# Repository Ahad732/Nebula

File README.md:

# RP2040 Devboard
I have made a devboard with RP 2040 microcontroller. It has 16 mb storage and its just like a raspberry pi pico but in my design. I had build it off a guide from macondo.I built it to learn hardware. This was my first hardware project for hackclub. It has a usb type C port that is used everywhere nowadays.

Features :
16 Mbit Storage    
Bootsel button  
Uses the popular RP2040 microcontroller    
Can be easily coded for custom projects and inovative ideas  
Open-source so anyone can use the design and order their board  
Has 2 leds, a power and a gpio led  

|Designator                                |Footprint                                  |Value                      |Quantity                   |Price                |Link                                                                                                                                                                 |
|------------------------------------------|-------------------------------------------|---------------------------|---------------------------|---------------------|---------------------------------------------------------------------------------------------------------------------------------------------------------------------|
|C1_2, C1, C10                             |402                                        |C 1uf                      |125                        |0.1                  |https://robu.in/product/cl05a105kq5nnwc-samsung-electro-mechanics-multilayer-ceramic-capacitors-mlcc-smd-smt-1uf-10-6-3v-x5r-1-0402/                                 |
|C11, C12, C3, C4, C5, C6, C7, C8, C9_2, C9|402                                        |C0.1uf                     |ALREADY HAVE               |---------------------|https://robu.in/product/0402b104j100ct-walsin-smd-multilayer-ceramic-capacitor-general-purpose-0-1-%c2%b5f-10-v-0402-1005-metric-%c2%b1-5-x7r/                       |
|C14                                       |603                                        |10 uF                      |ALREADY HAVE               |---------------------|https://robu.in/product/tcc0603x5r106m100ct-cctc-smt-ceramic-capacitors-0603-x5r-106m10%c2%b5f%c2%b120-rated-voltage10v-thickness0-80mm-tape/                        |
|C15, C16                                  |402                                        |33pF                       |30                         |0.11                 |https://robu.in/product/0402hq330j500nb-fh-smd-multilayer-ceramic-capacitor-33-pf-50-v-0402-1005-metric-%c2%b1-5-c0g/                                                |
|J1                                        |USB_C_Receptacle_XKB_U262-16XN-4BVC11      |USB_C_Receptacle_USB2.0_16P|ALREADY HAVE               |---------------------|https://www.lcsc.com/product-detail/C393939.html?s_z=n_q_c393939&globalKeyword=c393939                                                                               |
|J2, J3                                    |PinHeader_1x20_P2.54mm_Vertical            |Conn_01x20                 |2                          |DNP                  |                                                                                                                                                                     |
|J4                                        |PinHeader_1x03_P2.54mm_Vertical            |Conn_01x03                 |1                          |DNP                  |                                                                                                                                                                     |
|R1, R2                                    |402                                        |5.1K                       |100                        |0.11                 |https://robu.in/product/rc0402fr-075k1l-yageo-smd-chip-resistor/                                                                                                     |
|R3, R4                                    |402                                        |27                         |35                         |0.12                 |https://robu.in/product/0402wgj0270tce-uniohm-royal-ohm-62-5mw-thick-film-resistors-50v%c2%b1100ppm-%e2%84%83-%c2%b15-27%cf%89-0402-chip-resistor-surface-mount-rohs/|
|R5, R6, R7, R8                            |402                                        |1K                         |30                         |0.11                 |https://robu.in/product/wr04x1001ftl-walsin-62-5mw-thick-film-resistors-50v-%c2%b1100ppm-%e2%84%83-%c2%b11-1k%cf%89-0402-chip-resistor-surface-mount-rohs/           |
|R7                                        |402                                        |10K                        |85                         |0.11                 |https://robu.in/product/rc0402fr-0710kl-yageo-res-thick-film-0402-10k-ohm-1-0-063w1-16w-%c2%b1100ppm-c-pad-smd-t-r/                                                  |
|SW1                                       |Button_Switch_SMD:SW_SPST_PTS810           |SW_Push                    |5                          |0.99                 |https://robu.in/product/pts810sjg250smtrlfs-ck-3-2mm-2-5mm-round-button-50ma-standing-paste-4-2mm-spst-400gf-16v-smd-4p3-2x4-2mm-tactile-switches-rohs/              |
|U1                                        |QFN-56-1EP_7x7mm_P0.4mm_EP3.2x3.2mm        |RP2040                     |2                          |1.33                 |https://robu.in/product/raspberry-pi-rp2040/                                                                                                                         |
|U2                                        |Winbond_USON-8-1EP_3x2mm_P0.5mm_EP0.2x1.6mm|APS1604M-3SQRx-ZR          |2                          |4.88                 |https://www.lioncircuits.com/parts/IS25WP016D-JULE-TR                                                                                                                |
|U4                                        |SOT-23                                     |MCP1700x-330xxTT           |2                          |1.05                 |https://www.lioncircuits.com/parts/MCP1700T-3302E%2FTT                                                                                                               |
|Y1                                        |Crystal_SMD_3225-4Pin_3.2x2.5mm            |Crystal_GND24              |2                          |1.23                 |https://www.lioncircuits.com/parts/ECS-120-20-33-CKM-TR                                                                                                              |
|D1, D2                                    |Led                                        |402                        |----------------------     |ALREADY HAVE         |---------------------                                                                                                                                                |
|                                          |                                           |                           |Tools Required For Building|22.88                |https://robu.in/product/yihua-8858-v-hot-air-station-nozzles-stand/                                                                                                  |
|                                          |                                           |                           |PCB Cost + Shipping        |9.29                 |                                                                                                                                                                     |
|                                          |                                           |                           |Parts Shipping             |1.55                 |                                                                                                                                                                     |
|                                          |                                           |                           |Total                      |43.86                |                                                                                                                                                                     |

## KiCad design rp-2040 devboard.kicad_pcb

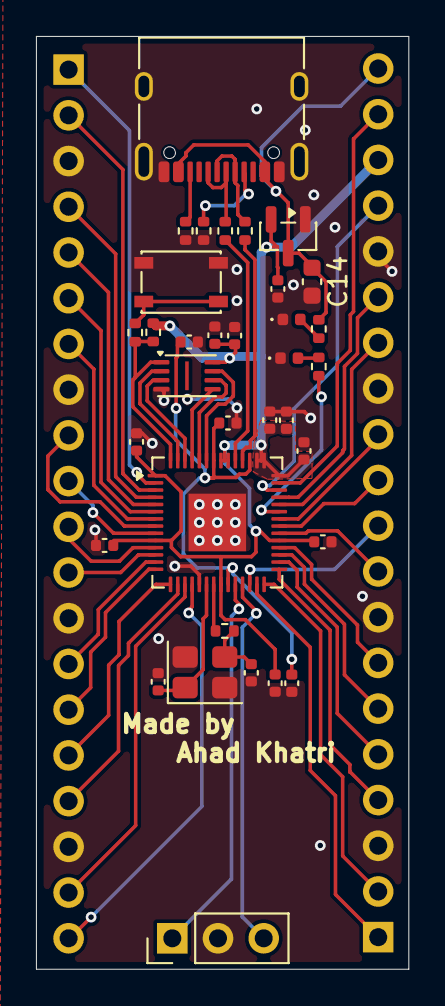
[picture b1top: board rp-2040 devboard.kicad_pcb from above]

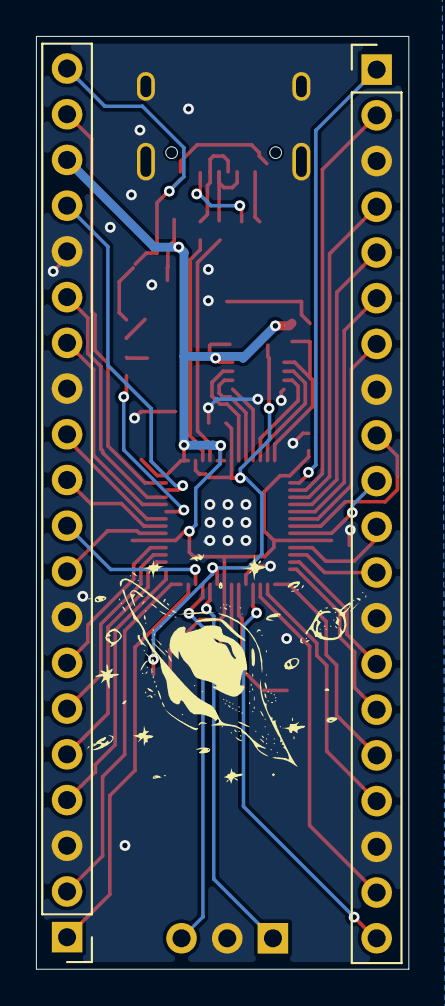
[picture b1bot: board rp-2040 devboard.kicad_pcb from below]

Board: 2 copper layers, 20.7 x 51.8 mm, 36 parts (2 on the bottom side), 55 nets.

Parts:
C1, C1#2, C10: C 1uf; C_0402_1005Metric
C3, C4, C5, C6, C7, C8, C9, C9#2, C11, C12: C0.1uf; C_0402_1005Metric
C14: 10 uF; C_0603_1608Metric
C15, C16: 33pF; C_0402_1005Metric
D1, D2: LED; LED_0402_1005Metric
J1: USB_C_Receptacle_USB2.0_16P; USB_C_Receptacle_XKB_U262-16XN-4BVC11
J2, J3: Conn_01x20; PinHeader_1x20_P2.54mm_Vertical
J4: Conn_01x03; PinHeader_1x03_P2.54mm_Vertical
R1, R2: 5.1K; R_0402_1005Metric
R3, R4: 27; R_0402_1005Metric
R5, R6, R8, R9: 1K; R_0402_1005Metric
R7: 10K; R_0402_1005Metric
SW1: SW_Push; SW_SPST_PTS810
U1: RP2040; QFN-56-1EP_7x7mm_P0.4mm_EP3.2x3.2mm
U2: APS1604M-3SQRx-ZR; Winbond_USON-8-1EP_3x2mm_P0.5mm_EP0.2x1.6mm
U4: MCP1700x-330xxTT; SOT-23
Y1: Crystal_GND24; Crystal_SMD_3225-4Pin_3.2x2.5mm

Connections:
+1V1: C10.1, C11.1, C12.1, U1.23 (DVDD), U1.45 (VREG_VOUT), U1.50 (DVDD)
+3V3: C1.1, C1#2.1, C3.1, C4.1, C5.1, C6.1, C7.1, C8.1, C9.1, C9#2.1, J3.18, R7.2, U1.1 (IOVDD), U1.10 (IOVDD), U1.22 (IOVDD), U1.33 (IOVDD), U1.42 (IOVDD), U1.43 (ADC_AVDD), U1.44 (VREG_VIN), U1.48 (USB_VDD), U1.49 (IOVDD), U2.8 (VDD), U4.2 (VO)
GND: C1.2, C1#2.2, C3.2, C4.2, C5.2, C6.2, C7.2, C8.2, C9.2, C9#2.2, C10.2, C11.2, C12.2, C14.2, C15.1, C16.1, D1.1 (K), D2.1 (K), J1.A1 (GND), J1.A12 (GND), J1.B1 (GND), J1.B12 (GND), J1.SH (SHIELD), J2.3, J2.8, J2.13, J2.18, J3.3, J3.8, J3.13, J3.16, J4.2, R1.1, R2.1, SW1.1, U1.19 (TESTEN), U1.57 (GND), U2.4 (VSS), U4.1 (GND), Y1.2 (G), Y1.4 (G)
GPIO0: J2.1, U1.2 (GPIO0)
GPIO1: J2.2, U1.3 (GPIO1)
GPIO2: J2.4, U1.4 (GPIO2)
GPIO3: J2.5, U1.5 (GPIO3)
GPIO4: J2.6, U1.6 (GPIO4)
GPIO5: J2.7, U1.7 (GPIO5)
GPIO6: J2.9, U1.8 (GPIO6)
GPIO7: J2.10, U1.9 (GPIO7)
GPIO8: J2.11, U1.11 (GPIO8)
GPIO9: J2.12, U1.12 (GPIO9)
GPIO10: J2.14, U1.13 (GPIO10)
GPIO11: J2.15, U1.14 (GPIO11)
GPIO12: J2.16, U1.15 (GPIO12)
GPIO13: J2.17, U1.16 (GPIO13)
GPIO14: J2.19, U1.17 (GPIO14)
GPIO15: J2.20, U1.18 (GPIO15)
GPIO16: J3.1, U1.27 (GPIO16)
GPIO17: J3.2, U1.28 (GPIO17)
GPIO18: J3.4, U1.29 (GPIO18)
GPIO19: J3.5, U1.30 (GPIO19)
GPIO20: J3.6, U1.31 (GPIO20)
GPIO21: J3.7, U1.32 (GPIO21)
GPIO22: J3.9, U1.34 (GPIO22)
GPIO23: J3.11, U1.35 (GPIO23)
GPIO24: J3.12, U1.36 (GPIO24)
GPIO25: R9.1, U1.37 (GPIO25)
GPIO26/ADC0: J3.14, U1.38 (GPIO26/ADC0)
GPIO27/ADC1: J3.15, U1.39 (GPIO27/ADC1)
GPIO28/ADC2: J3.17, U1.40 (GPIO28/ADC2)
GPIO29/ADC3: J3.19, U1.41 (GPIO29/ADC3)
unnamed: C15.2, R5.1, Y1.3
unnamed: D1.2 (A), R8.2
unnamed: D2.2 (A), R9.2
unnamed: J1.A5 (CC1), R2.2
unnamed: J1.B5 (CC2), R1.2
unnamed: R6.1, SW1.2
unnamed: R3.1, U1.46 (USB_DM)
unnamed: R4.1, U1.47 (USB_DP)
QSPI_SCLK: U1.52 (QSPI_SCLK), U2.6 (SCLK)
QSPI_SD0: U1.53 (QSPI_SD0), U2.5 (SI/SIO0)
QSPI_SD1: U1.55 (QSPI_SD1), U2.2 (SO/SIO1)
QSPI_SD2: U1.54 (QSPI_SD2), U2.3 (SIO2)
QSPI_SD3: U1.51 (QSPI_SD3), U2.7 (SIO3)
QSPI_SS: R6.2, R7.1, U1.56 (~QSPI_SS), U2.1 (~CE)
RUN: J3.10, U1.26 (RUN)
SWCLK: J4.1, U1.24 (SWCLK)
SWDIO: J4.3, U1.25 (SWDIO)
USB_D+: J1.A6 (D+), J1.B6 (D+), R4.2
USB_D-: J1.A7 (D-), J1.B7 (D-), R3.2
VBUS: C14.1, J1.A4 (VBUS), J1.A9 (VBUS), J1.B4 (VBUS), J1.B9 (VBUS), J3.20, R8.1, U4.3 (VI)
XIN: C16.2, U1.20 (XIN), Y1.1
XOUT: R5.2, U1.21 (XOUT)

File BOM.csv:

Designator,Footprint,Value,Quantity,Price,Link
"C1_2, C1, C10",402,C 1uf,125,0.1,https://robu.in/product/cl05a105kq5nnwc-samsung-electro-mech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
"C11, C12, C3, C4, C5, C6, C7, C8, C9_2, C9",402,C0.1uf,ALREADY HAVE,---------------------,https://robu.in/product/0402b104j100ct-walsin-smd-multilayer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
C14,603,10 uF,ALREADY HAVE,---------------------,https://robu.in/product/tcc0603x5r106m100ct-cctc-smt-ceramic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
"C15, C16",402,33pF,30,0.11,https://robu.in/product/0402hq330j500nb-fh-smd-multilayer-ce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
J1,USB_C_Receptacle_XKB_U262-16XN-4BVC11,USB_C_Receptacle_USB2.0_16P,ALREADY HAVE,---------------------,https://www.lcsc.com/product-detail/C393939.html?s_z=n_q_c39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
"J2, J3",PinHeader_1x20_P2.54mm_Vertical,Conn_01x20,2,DNP,
J4,PinHeader_1x03_P2.54mm_Vertical,Conn_01x03,1,DNP,
"R1, R2",402,5.1K,100,0.11,https://robu.in/product/rc0402fr-075k1l-yageo-smd-chip-resistor/
"R3, R4",402,27,35,0.12,https://robu.in/product/0402wgj0270tce-uniohm-royal-ohm-62-5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
"R5, R6, R7, R8",402,1K,30,0.11,https://robu.in/product/wr04x1001ftl-walsin-62-5mw-thick-fil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
R7,402,10K,85,0.11,https://robu.in/product/rc0402fr-0710kl-yageo-res-thick-film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
SW1,Button_Switch_SMD:SW_SPST_PTS810,SW_Push,5,0.99,https://robu.in/product/pts810sjg250smtrlfs-ck-3-2mm-2-5mm-r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
U1,QFN-56-1EP_7x7mm_P0.4mm_EP3.2x3.2mm,RP2040,2,1.33,https://robu.in/product/raspberry-pi-rp2040/
U2,Winbond_USON-8-1EP_3x2mm_P0.5mm_EP0.2x1.6mm,APS1604M-3SQRx-ZR,2,4.88,https://www.lioncircuits.com/parts/IS25WP016D-JULE-TR
U4,SOT-23,MCP1700x-330xxTT,2,1.05,https://www.lioncircuits.com/parts/MCP1700T-3302E%2FTT
Y1,Crystal_SMD_3225-4Pin_3.2x2.5mm,Crystal_GND24,2,1.23,https://www.lioncircuits.com/parts/ECS-120-20-33-CKM-TR
"D1, D2",Led,402,----------------------,ALREADT HAVE,---------------------
,,,Tools Required For Building,22.88,https://robu.in/product/yihua-8858-v-hot-air-station-nozzles-stand/
,,,PCB Cost + Shipping,9.29,
,,,Parts Shipping,1.55,
,,,Total,43.86,
